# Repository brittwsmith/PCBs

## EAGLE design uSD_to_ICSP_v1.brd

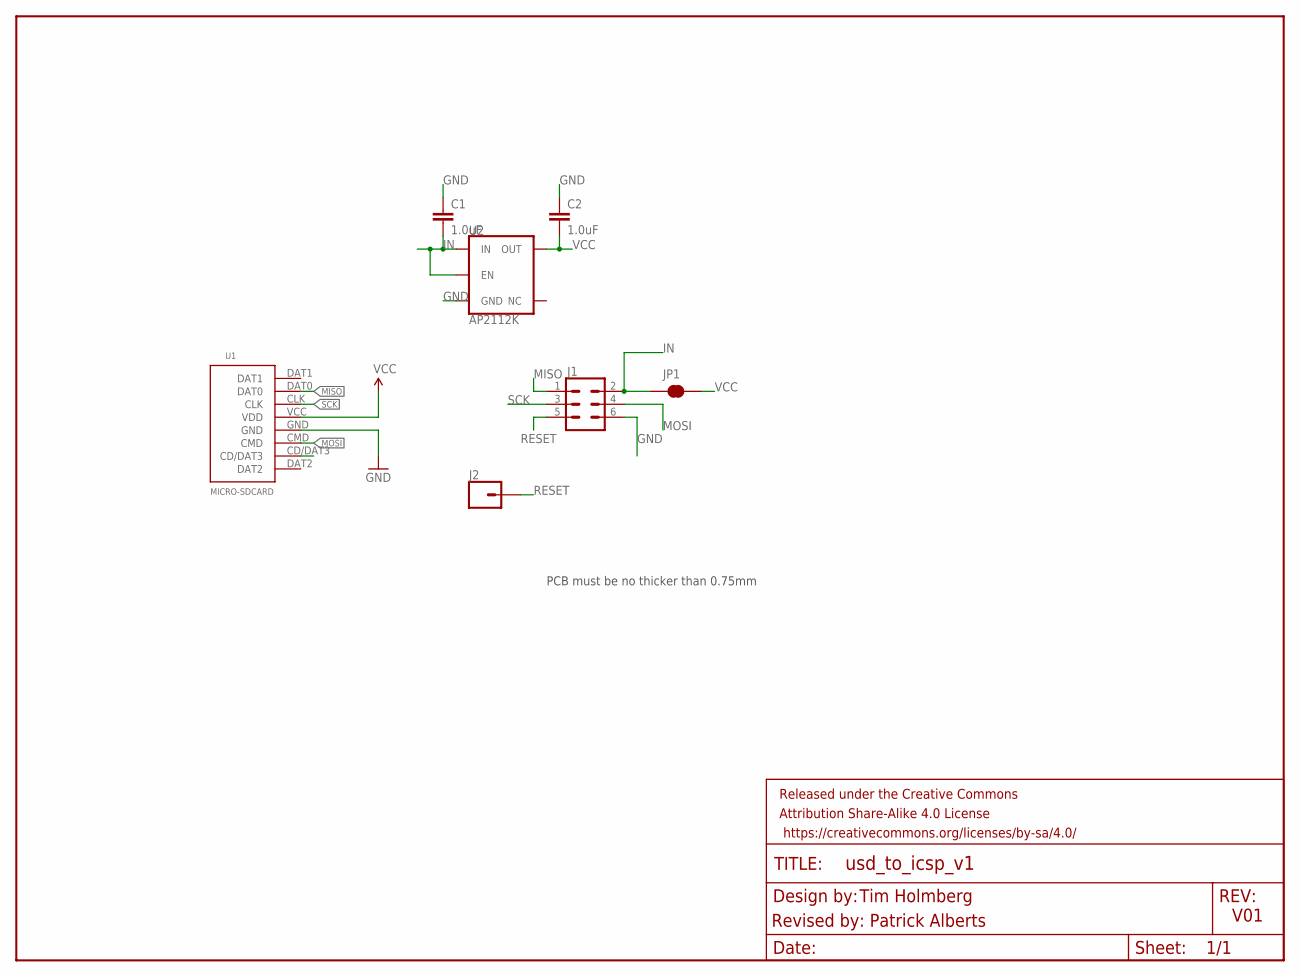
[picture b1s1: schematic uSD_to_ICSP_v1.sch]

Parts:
C1, C2: 1.0uF; 0805
FRAME1: FRAME-LETTER; CREATIVE_COMMONS
J1: CONN_03X2NO_SILK; 2X3-NS
J2: CONN_01PTH_LONGPAD; 1X01_LONGPAD
JP1: JUMPER-SMT_2_NC_TRACE_NO-SILK; SMT-JUMPER_2_NC_TRACE_NO-SILK
U1: MICRO-SDCARD
U2: AP2112K; SOT23-5

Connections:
CD/DAT3: U1.CD/DAT3
GND: C1.1, C2.1, J1.6, U1.GND, U2.2 (GND)
IN: C1.2, J1.2, JP1.1, U2.1 (IN), U2.3 (EN)
MISO: J1.1, U1.DAT0
MOSI: J1.4, U1.CMD
RESET: J1.5, J2.1
SCK: J1.3, U1.CLK
VCC: C2.2, JP1.2, U1.VCC (VDD), U2.5 (OUT)

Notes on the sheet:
PCB must be no thicker than 0.75mm
V01
Revised by: Patrick Alberts
Tim Holmberg

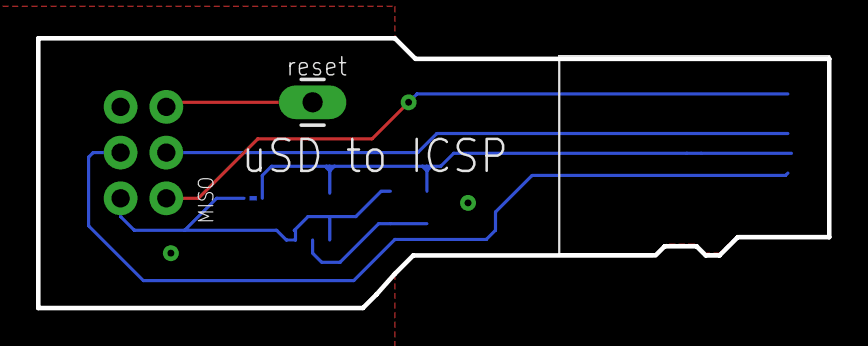
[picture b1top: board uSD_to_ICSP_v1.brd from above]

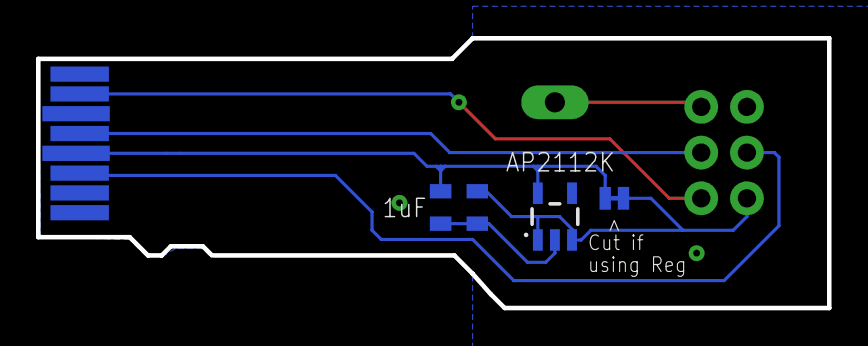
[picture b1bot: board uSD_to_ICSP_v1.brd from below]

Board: 2 copper layers, 43.9 x 15.0 mm, 8 parts (4 on the bottom side), 7 nets.

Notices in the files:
parts and their libraries:
SparkFun-Aesthetics: Licensing: Creative Commons ShareAlike 4.0 International - https://creativecommons.org/licenses/by-sa/4.0
SparkFun-Aesthetics: Released under the Creative Commons Attribution Share-Alike 4.0 License
SparkFun-Aesthetics: https://creativecommons.org/licenses/by-sa/4.0
